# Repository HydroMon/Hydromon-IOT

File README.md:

# Hydromon-IOT
This repo is used to cover all work related to IOT

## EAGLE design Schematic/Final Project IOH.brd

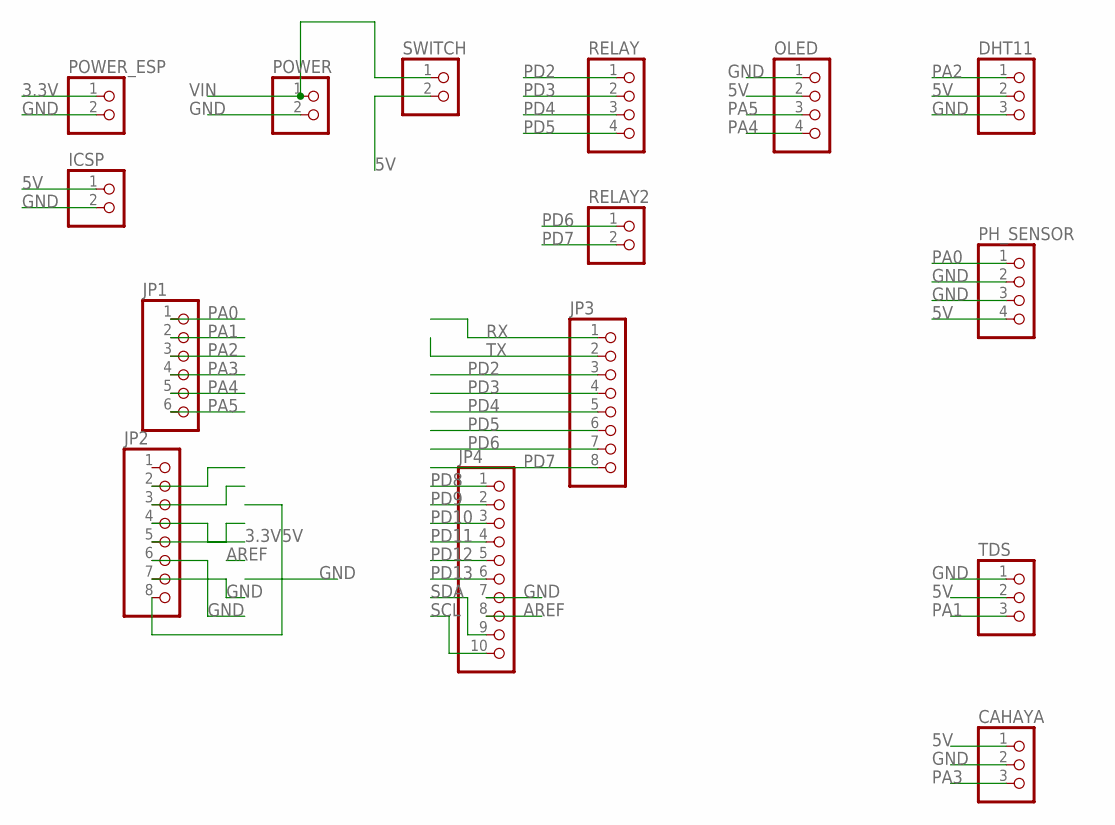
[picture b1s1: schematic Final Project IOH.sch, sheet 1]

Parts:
CAHAYA: PINHD-1X3; 1X03
DHT11: PINHD-1X3; 1X03
ICSP: PINHD-1X2; 1X02
JP1: PINHD-1X6; 1X06
JP2, JP3: PINHD-1X8; 1X08
JP4: PINHD-1X10; 1X10
OLED: PINHD-1X4; 1X04
PH_SENSOR: PINHD-1X4; 1X04
POWER: PINHD-1X2; 1X02
POWER_ESP: PINHD-1X2; 1X02
RELAY: PINHD-1X4; 1X04
RELAY2: PINHD-1X2; 1X02
SWITCH: PINHD-1X2; 1X02
TDS: PINHD-1X3; 1X03

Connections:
3.3V: JP2.4, POWER_ESP.1
5V: CAHAYA.1, DHT11.2, ICSP.1, JP2.8, OLED.2, PH_SENSOR.4, SWITCH.2, TDS.2
AREF: JP4.8
GND: CAHAYA.2, DHT11.3, ICSP.2, JP2.6, JP2.7, JP4.7, OLED.1, PH_SENSOR.2, PH_SENSOR.3, POWER.2, POWER_ESP.2, TDS.1
PA0: JP1.1, PH_SENSOR.1
PA1: JP1.2, TDS.3
PA2: DHT11.1, JP1.3
PA3: CAHAYA.3, JP1.4
PA4: JP1.5, OLED.4
PA5: JP1.6, OLED.3
PD2: JP3.3, RELAY.1
PD3: JP3.4, RELAY.2
PD4: JP3.5, RELAY.3
PD5: JP3.6, RELAY.4
PD6: JP3.7, RELAY2.1
PD7: JP3.8, RELAY2.2
PD8: JP4.1
PD9: JP4.2
PD10: JP4.3
PD11: JP4.4
PD12: JP4.5
PD13: JP4.6
RX: JP3.1
SCL: JP4.10
SDA: JP4.9
TX: JP3.2
VIN: POWER.1, SWITCH.1

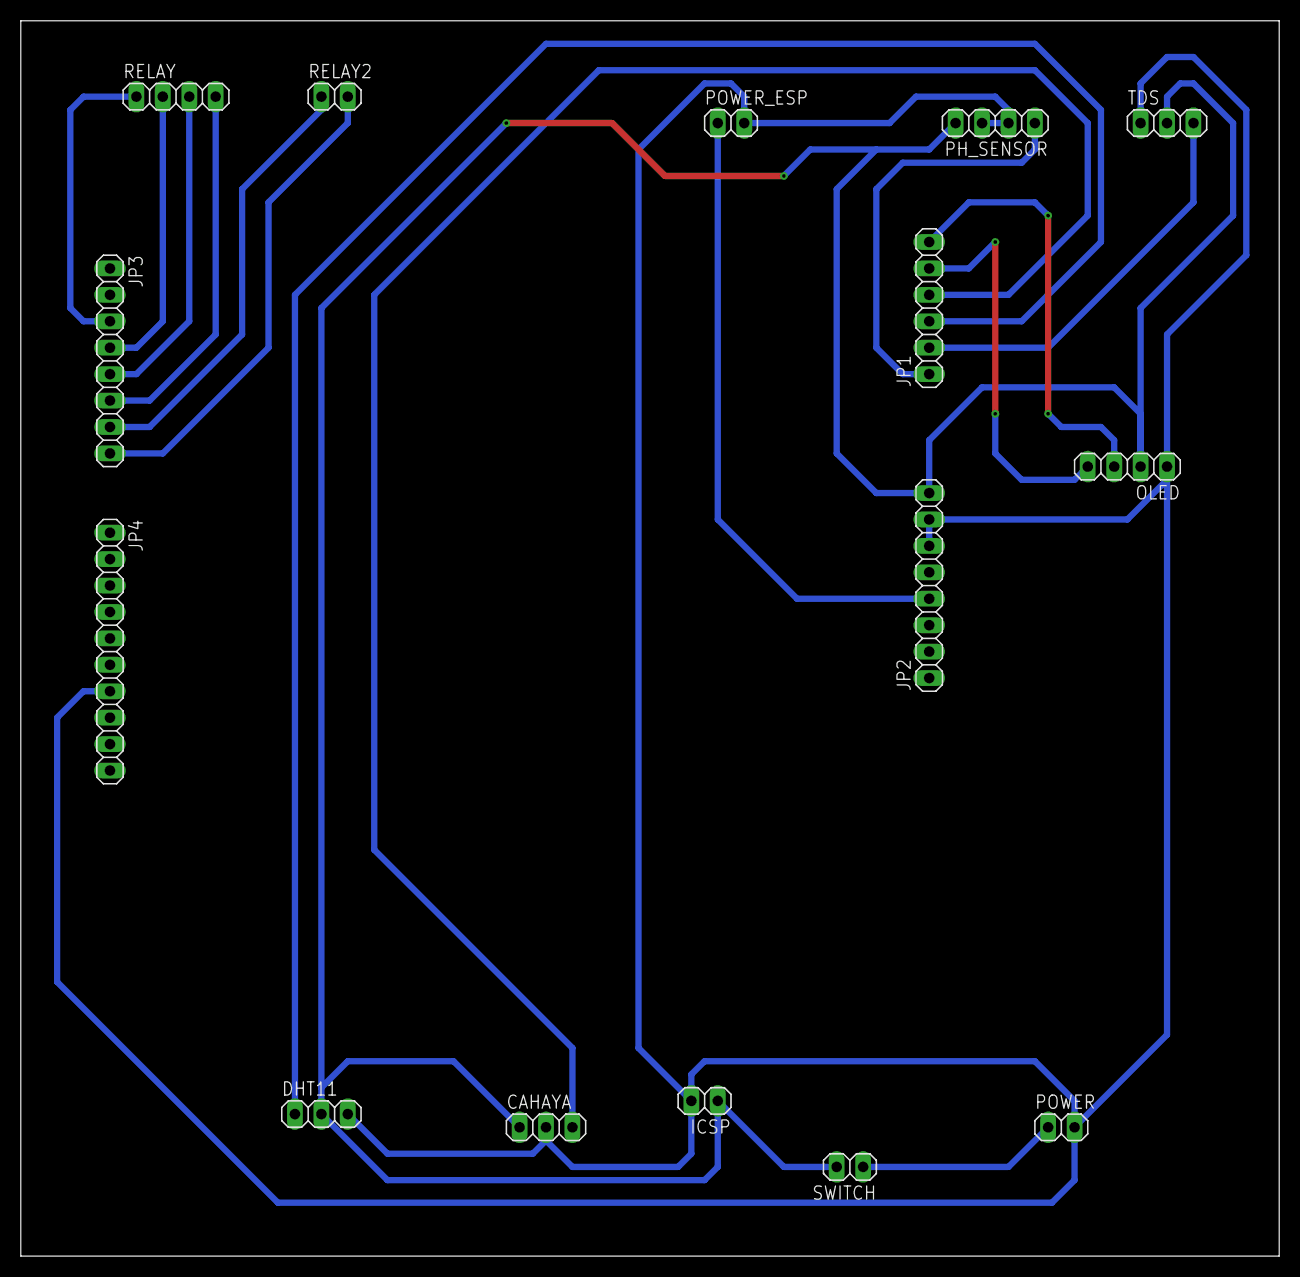
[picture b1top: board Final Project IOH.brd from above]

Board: 2 copper layers, 121.0 x 118.7 mm, 15 parts (0 on the bottom side), 16 nets.

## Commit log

2022-06-07 Create Schematic
2022-06-07 Create Delete
